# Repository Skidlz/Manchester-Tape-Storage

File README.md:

# Micro Manchester Tape Storage
Tools for storing binary data on cassette

Includes:
  - Python script for encoding
  - Arduino sketch for decoding
  - Eagle CAD files for a hardware interface
  - Images of schematic and board

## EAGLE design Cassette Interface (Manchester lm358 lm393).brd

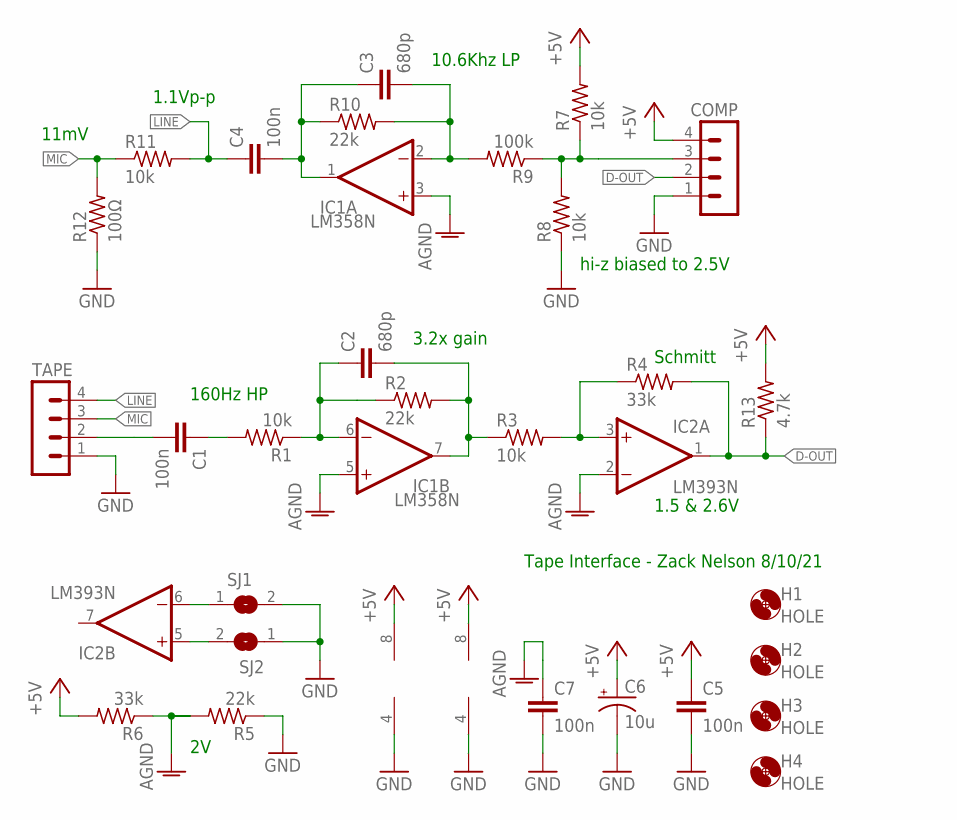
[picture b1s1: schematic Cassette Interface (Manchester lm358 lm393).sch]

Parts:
C1, C4, C5, C7: 100n; C025-024X044
C2, C3: 680p; C025-024X044
C6: 10u; E2,5-5
COMP: MA04-1
H1, H2, H3, H4: HOLE; 3,0
IC1: LM358N; DIL08
IC2: LM393N; DIL08
R1, R3, R7, R8, R11: 10k; 0204V
R2, R5, R10: 22k; 0204V
R4, R6: 33k; 0204V
R9: 100k; 0204V
R12: 100Ω; 0204V
R13: 4.7k; 0204V
SJ1, SJ2: SJ
TAPE: MA04-1

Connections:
+5V: C5.1, C6.+, COMP.4, IC1.8 (V+), IC2.8 (V+), R6.2, R7.2, R13.2
AGND: C7.1, IC1.3 (+IN), IC1.5 (+IN), IC2.2 (-IN), R5.2, R6.1
D-IN: COMP.3, R7.1, R8.2, R9.1
D-OUT: COMP.2, IC2.1 (OUT), R4.2, R13.1
GND: C5.2, C6.-, C7.2, COMP.1, IC1.4 (V-), IC2.4 (V-), R5.1, R8.1, R12.1, SJ1.2, SJ2.1, TAPE.1
LINE: C4.1, R11.2, TAPE.4
MIC: R11.1, R12.2, TAPE.3
unnamed: C1.1, R1.2
unnamed: C2.1, IC1.6 (-IN), R1.1, R2.1
unnamed: IC2.6 (-IN), SJ1.1
unnamed: C2.2, IC1.7 (OUT), R2.2, R3.1
unnamed: IC2.5 (+IN), SJ2.2
unnamed: IC2.3 (+IN), R3.2, R4.1
unnamed: C3.2, IC1.2 (-IN), R9.2, R10.2
unnamed: C3.1, C4.2, IC1.1 (OUT), R10.1
TAPE-IN: C1.2, TAPE.2

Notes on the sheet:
10.6Khz LP
1.1Vp-p
hi-z biased to 2.5V
160Hz HP
Tape Interface - Zack Nelson 8/10/21
Schmitt
1.5 & 2.6V
3.2x gain
11mV

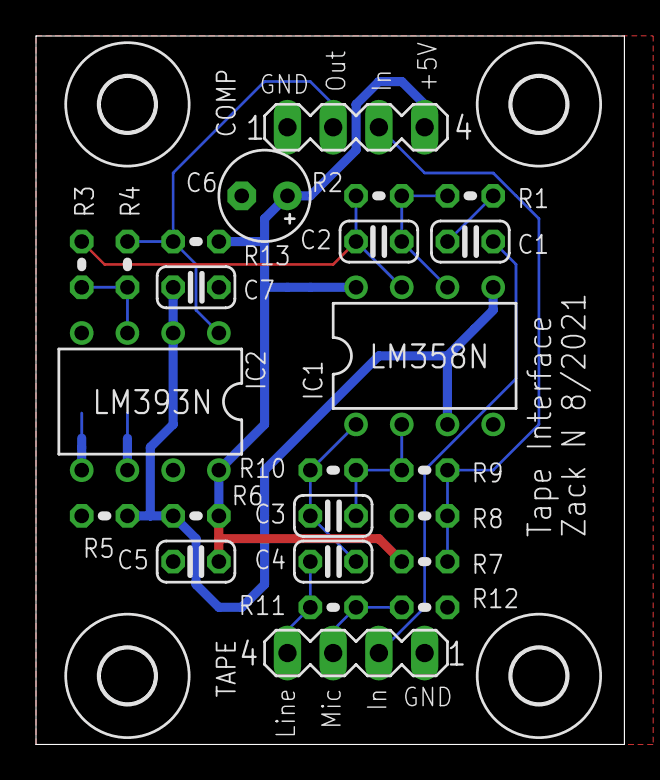
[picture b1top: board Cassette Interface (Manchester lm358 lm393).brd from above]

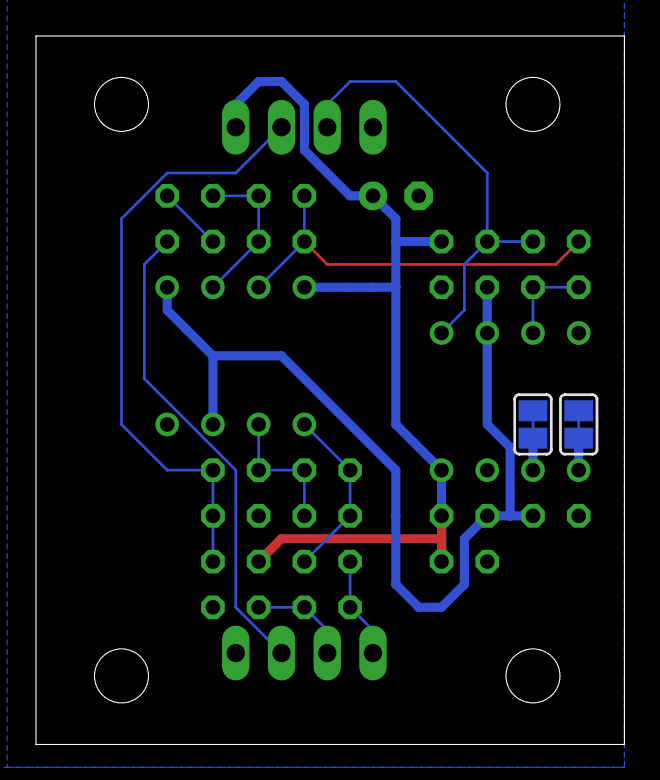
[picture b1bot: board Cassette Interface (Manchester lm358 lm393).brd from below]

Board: 2 copper layers, 32.7 x 39.4 mm, 30 parts (2 on the bottom side), 16 nets.
